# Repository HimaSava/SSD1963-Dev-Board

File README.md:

# SSD1963-Dev-Board

SSD1963 is a cheap LCD display chip. It is easy to use and it is preety cheap when compared to the others out there.
Unluckyly being cheap comes with it's flaws. The chip comes in a 128 pin QFP and is hard for beginners to solder without the right tools. But the biggest issue is PCB layout. Unless you are cutting corners on decaps the chip needs 40 seperate D-Caps.
And the worst part there is no guidelines of a dev board with any kind of layout out there to help the beginners.
Well through multiple revisions and sheer luck I designed the whole dev board and had it manufactured and tested.
To my surprise it works with out any hitchs. So I am sharing the files here. 

## Now some specs on the actual Dev Board:
It has the SSD1963 chip and also has the TSC2046 Touch Sensor chip.

The dev board was designed with a particular display(resistive touch) in mind and I have attached the datasheet for it. Based on your display you may need to change the LCD connector.

In interfacing the SSD1963 is used in 8080 mode(Check datasheet) and the touch sensor uses SPI protocol. For now I have added a FRC connector with all the pins that are needed to drive the board, if you want to change it be my guest.

Right now I am still making modifications to the board, so expect some changes in the future and also ping me if you have any suggestions.

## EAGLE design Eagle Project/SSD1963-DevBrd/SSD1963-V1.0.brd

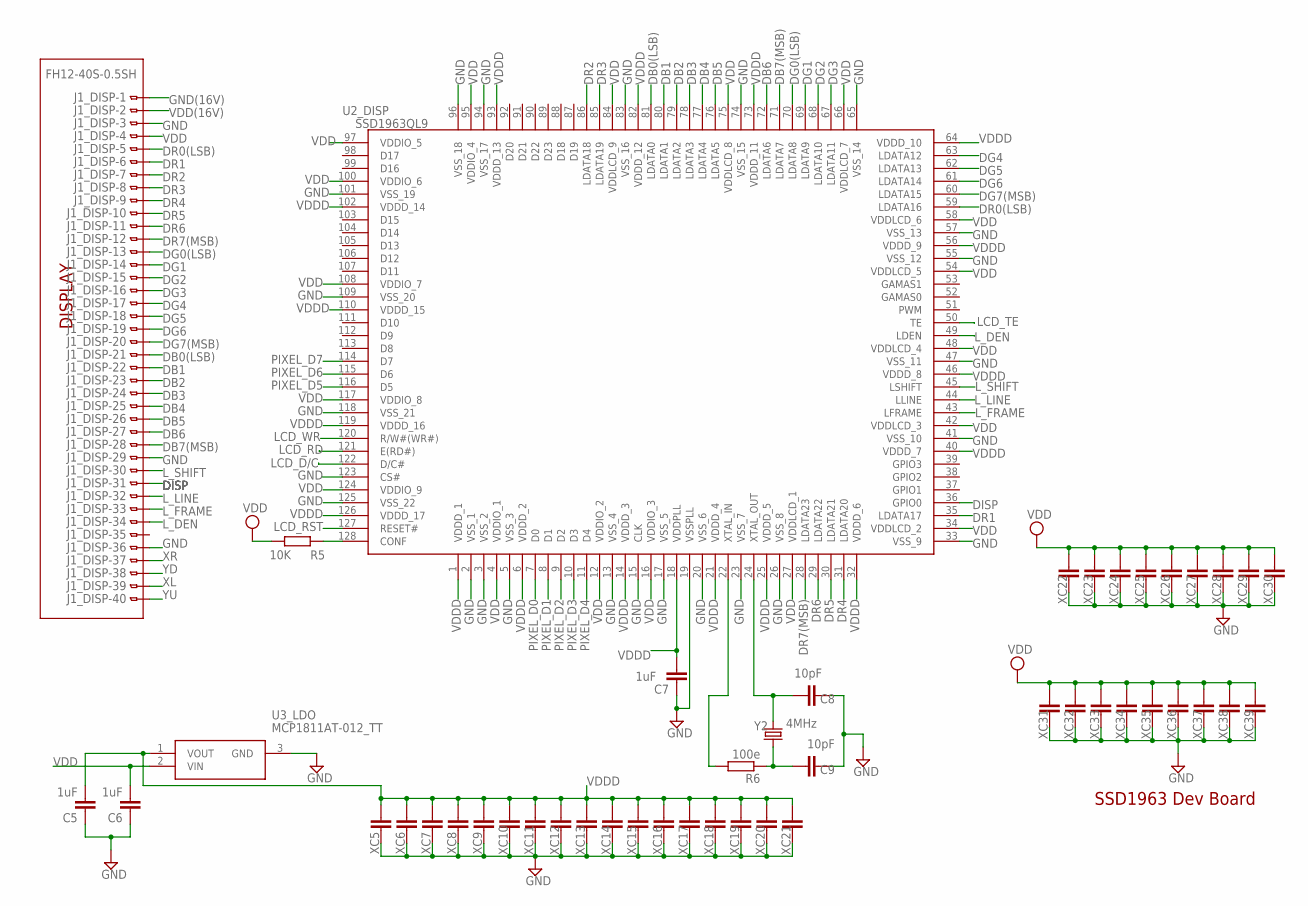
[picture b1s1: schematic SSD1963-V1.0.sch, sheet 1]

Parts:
C5, C6: 1uF; C1206
C7: 1uF; C0805
C8, C9: 10pF; C1206
J1_DISP: FH12-40S-0.5SH
R5: 10K; R1206
R6: 100e; R0805
U2_DISP: SSD1963QL9; QFP40P1600X1600X160-128N
U3_LDO: MCP1811AT-012_TT; SOT95P237X112-3N
XC5, XC6, XC7, XC8, XC9, XC10, XC11, XC12, XC13, XC14, XC15, XC16, XC17, XC18, XC19, XC20, XC21, XC22, XC23, XC24, XC25, XC26, XC27, XC28, XC29, XC30, XC31, XC32, XC33, XC34, XC35, XC36, XC37, XC38, XC39: 0.1uF; C0805
Y2: 4MHz; HC49UP

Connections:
DB0(LSB): J1_DISP.20, U2_DISP.81 (LDATA0)
DB1: J1_DISP.19, U2_DISP.80 (LDATA1)
DB2: J1_DISP.18, U2_DISP.79 (LDATA2)
DB3: J1_DISP.17, U2_DISP.78 (LDATA3)
DB4: J1_DISP.16, U2_DISP.77 (LDATA4)
DB5: J1_DISP.15, U2_DISP.76 (LDATA5)
DB6: J1_DISP.14, U2_DISP.72 (LDATA6)
DB7(MSB): J1_DISP.13, U2_DISP.71 (LDATA7)
DG0(LSB): J1_DISP.28, U2_DISP.70 (LDATA8)
DG1: J1_DISP.27, U2_DISP.69 (LDATA9)
DG2: J1_DISP.26, U2_DISP.68 (LDATA10)
DG3: J1_DISP.25, U2_DISP.67 (LDATA11)
DG4: J1_DISP.24, U2_DISP.63 (LDATA12)
DG5: J1_DISP.23, U2_DISP.62 (LDATA13)
DG6: J1_DISP.22, U2_DISP.61 (LDATA14)
DG7(MSB): J1_DISP.21, U2_DISP.60 (LDATA15)
DISP: J1_DISP.10, U2_DISP.36 (GPIO0)
DR0(LSB): J1_DISP.36, U2_DISP.59 (LDATA16)
DR1: J1_DISP.35, U2_DISP.35 (LDATA17)
DR2: J1_DISP.34, U2_DISP.86 (LDATA18)
DR3: J1_DISP.33, U2_DISP.85 (LDATA19)
DR4: J1_DISP.32, U2_DISP.31 (LDATA20)
DR5: J1_DISP.31, U2_DISP.30 (LDATA21)
DR6: J1_DISP.30, U2_DISP.29 (LDATA22)
DR7(MSB): J1_DISP.29, U2_DISP.28 (LDATA23)
GND: C5.1, C6.1, C7.1, C8.1, C9.1, J1_DISP.5, J1_DISP.12, J1_DISP.38, U2_DISP.2 (VSS_1), U2_DISP.3 (VSS_2), U2_DISP.5 (VSS_3), U2_DISP.13 (VSS_4), U2_DISP.15 (CLK), U2_DISP.17 (VSS_5), U2_DISP.19 (VSSPLL), U2_DISP.20 (VSS_6), U2_DISP.23 (VSS_7), U2_DISP.26 (VSS_8), U2_DISP.33 (VSS_9), U2_DISP.41 (VSS_10), U2_DISP.47 (VSS_11), U2_DISP.55 (VSS_12), U2_DISP.57 (VSS_13), U2_DISP.65 (VSS_14), U2_DISP.74 (VSS_15), U2_DISP.83 (VSS_16), U2_DISP.94 (VSS_17), U2_DISP.96 (VSS_18), U2_DISP.101 (VSS_19), U2_DISP.109 (VSS_20), U2_DISP.118 (VSS_21), U2_DISP.123 (CS#), U2_DISP.125 (VSS_22), U3_LDO.3 (GND), XC5.1, XC6.1, XC7.1, XC8.1, XC9.1, XC10.1, XC11.1, XC12.1, XC13.1, XC14.1, XC15.1, XC16.1, XC17.1, XC18.1, XC19.1, XC20.1, XC21.1, XC22.1, XC23.1, XC24.1, XC25.1, XC26.1, XC27.1, XC28.1, XC29.1, XC30.1, XC31.1, XC32.1, XC33.1, XC34.1, XC35.1, XC36.1, XC37.1, XC38.1, XC39.1; also elsewhere on the board
GND(16V): J1_DISP.40; also elsewhere on the board
LCD_D/C: U2_DISP.122 (D/C#); also elsewhere on the board
LCD_RD: U2_DISP.121 (E(RD#)); also elsewhere on the board
LCD_RST: U2_DISP.127 (RESET#); also elsewhere on the board
LCD_TE: U2_DISP.50 (TE); also elsewhere on the board
LCD_WR: U2_DISP.120 (R/W#(WR#)); also elsewhere on the board
L_DEN: J1_DISP.7, U2_DISP.49 (LDEN)
L_FRAME: J1_DISP.8, U2_DISP.43 (LFRAME)
L_LINE: J1_DISP.9, U2_DISP.44 (LLINE)
L_SHIFT: J1_DISP.11, U2_DISP.45 (LSHIFT)
unnamed: R5.1, U2_DISP.128 (CONF)
unnamed: C8.2, U2_DISP.24 (XTAL_OUT), Y2.2
unnamed: C9.2, R6.1, Y2.1
unnamed: R6.2, U2_DISP.22 (XTAL_IN)
PIXEL_D0: U2_DISP.7 (D0); also elsewhere on the board
PIXEL_D1: U2_DISP.8 (D1); also elsewhere on the board
PIXEL_D2: U2_DISP.9 (D2); also elsewhere on the board
PIXEL_D3: U2_DISP.10 (D3); also elsewhere on the board
PIXEL_D4: U2_DISP.11 (D4); also elsewhere on the board
PIXEL_D5: U2_DISP.116 (D5); also elsewhere on the board
PIXEL_D6: U2_DISP.115 (D6); also elsewhere on the board
PIXEL_D7: U2_DISP.114 (D7); also elsewhere on the board
VDD: C6.2, J1_DISP.37, R5.2, U2_DISP.4 (VDDIO_1), U2_DISP.12 (VDDIO_2), U2_DISP.16 (VDDIO_3), U2_DISP.27 (VDDLCD_1), U2_DISP.34 (VDDLCD_2), U2_DISP.42 (VDDLCD_3), U2_DISP.48 (VDDLCD_4), U2_DISP.54 (VDDLCD_5), U2_DISP.58 (VDDLCD_6), U2_DISP.66 (VDDLCD_7), U2_DISP.75 (VDDLCD_8), U2_DISP.84 (VDDLCD_9), U2_DISP.95 (VDDIO_4), U2_DISP.97 (VDDIO_5), U2_DISP.100 (VDDIO_6), U2_DISP.108 (VDDIO_7), U2_DISP.117 (VDDIO_8), U2_DISP.124 (VDDIO_9), U3_LDO.2 (VIN), XC22.2, XC23.2, XC24.2, XC25.2, XC26.2, XC27.2, XC28.2, XC29.2, XC30.2, XC31.2, XC32.2, XC33.2, XC34.2, XC35.2, XC36.2, XC37.2, XC38.2, XC39.2; also elsewhere on the board
VDD(16V): J1_DISP.39; also elsewhere on the board
VDDD: C5.2, C7.2, U2_DISP.1 (VDDD_1), U2_DISP.6 (VDDD_2), U2_DISP.14 (VDDD_3), U2_DISP.18 (VDDPLL), U2_DISP.21 (VDDD_4), U2_DISP.25 (VDDD_5), U2_DISP.32 (VDDD_6), U2_DISP.40 (VDDD_7), U2_DISP.46 (VDDD_8), U2_DISP.56 (VDDD_9), U2_DISP.64 (VDDD_10), U2_DISP.73 (VDDD_11), U2_DISP.82 (VDDD_12), U2_DISP.93 (VDDD_13), U2_DISP.102 (VDDD_14), U2_DISP.110 (VDDD_15), U2_DISP.119 (VDDD_16), U2_DISP.126 (VDDD_17), U3_LDO.1 (VOUT), XC5.2, XC6.2, XC7.2, XC8.2, XC9.2, XC10.2, XC11.2, XC12.2, XC13.2, XC14.2, XC15.2, XC16.2, XC17.2, XC18.2, XC19.2, XC20.2, XC21.2
XL: J1_DISP.2; also elsewhere on the board
XR: J1_DISP.4; also elsewhere on the board
YD: J1_DISP.3; also elsewhere on the board
YU: J1_DISP.1; also elsewhere on the board

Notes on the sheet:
DISPLAY
SSD1963 Dev Board

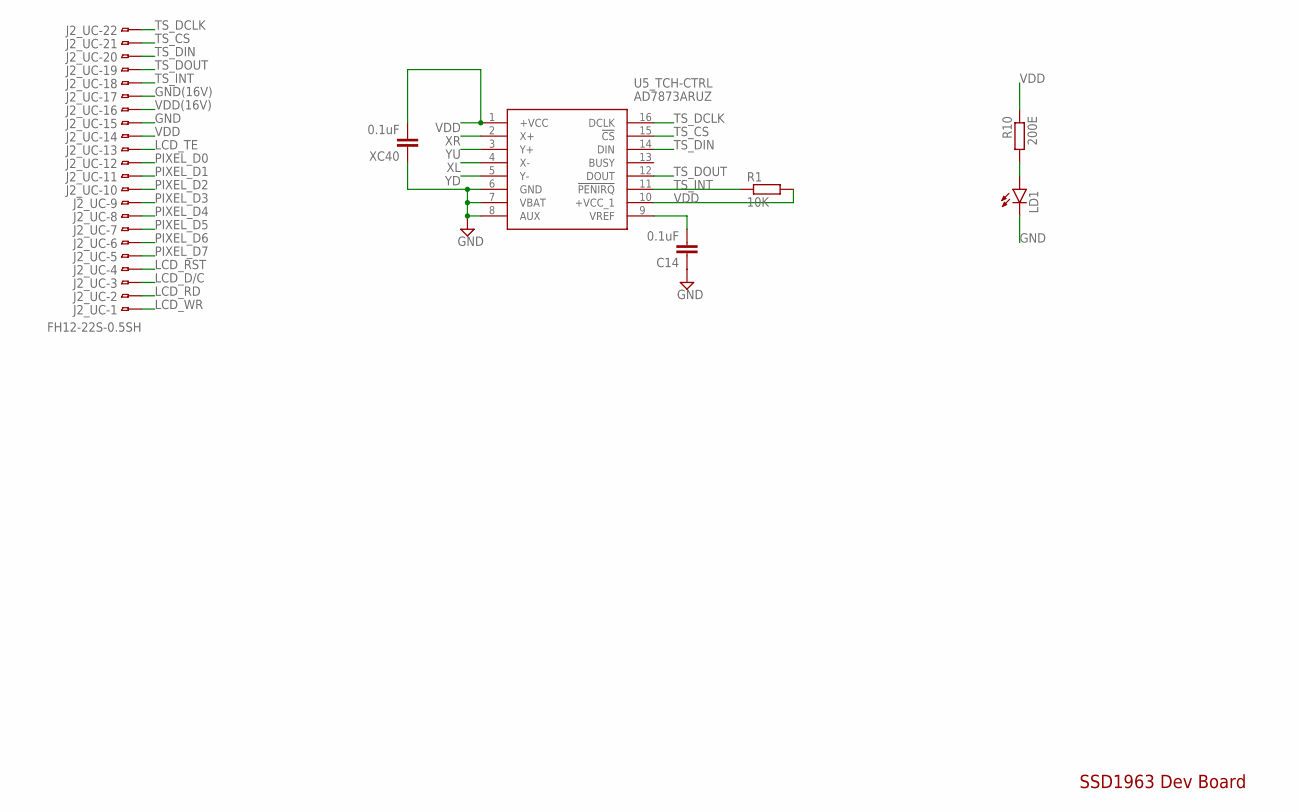
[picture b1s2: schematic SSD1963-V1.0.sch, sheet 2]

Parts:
C14: 0.1uF; C1206
J2_UC: FH12-22S-0.5SH
LD1: LEDCHIPLED_1206; CHIPLED_1206
R1: 10K; R1206
R10: 200E; R1206
U5_TCH-CTRL: AD7873ARUZ; SOP64P600X175-16N
XC40: 0.1uF; C0805

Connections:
GND: C14.1, J2_UC.15, LD1.C, U5_TCH-CTRL.6 (GND), U5_TCH-CTRL.7 (VBAT), U5_TCH-CTRL.8 (AUX), XC40.1; also elsewhere on the board
GND(16V): J2_UC.17; also elsewhere on the board
LCD_D/C: J2_UC.3; also elsewhere on the board
LCD_RD: J2_UC.2; also elsewhere on the board
LCD_RST: J2_UC.4; also elsewhere on the board
LCD_TE: J2_UC.13; also elsewhere on the board
LCD_WR: J2_UC.1; also elsewhere on the board
unnamed: C14.2, U5_TCH-CTRL.9 (VREF)
unnamed: LD1.A, R10.2
PIXEL_D0: J2_UC.12; also elsewhere on the board
PIXEL_D1: J2_UC.11; also elsewhere on the board
PIXEL_D2: J2_UC.10; also elsewhere on the board
PIXEL_D3: J2_UC.9; also elsewhere on the board
PIXEL_D4: J2_UC.8; also elsewhere on the board
PIXEL_D5: J2_UC.7; also elsewhere on the board
PIXEL_D6: J2_UC.6; also elsewhere on the board
PIXEL_D7: J2_UC.5; also elsewhere on the board
TS_CS: J2_UC.21, U5_TCH-CTRL.15 (!CS)
TS_DCLK: J2_UC.22, U5_TCH-CTRL.16 (DCLK)
TS_DIN: J2_UC.20, U5_TCH-CTRL.14 (DIN)
TS_DOUT: J2_UC.19, U5_TCH-CTRL.12 (DOUT)
TS_INT: J2_UC.18, R1.1, U5_TCH-CTRL.11 (!PENIRQ)
VDD: J2_UC.14, R1.2, R10.1, U5_TCH-CTRL.1 (+VCC), U5_TCH-CTRL.10 (+VCC_1), XC40.2; also elsewhere on the board
VDD(16V): J2_UC.16; also elsewhere on the board
XL: U5_TCH-CTRL.4 (X-); also elsewhere on the board
XR: U5_TCH-CTRL.2 (X+); also elsewhere on the board
YD: U5_TCH-CTRL.5 (Y-); also elsewhere on the board
YU: U5_TCH-CTRL.3 (Y+); also elsewhere on the board

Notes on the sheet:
SSD1963 Dev Board

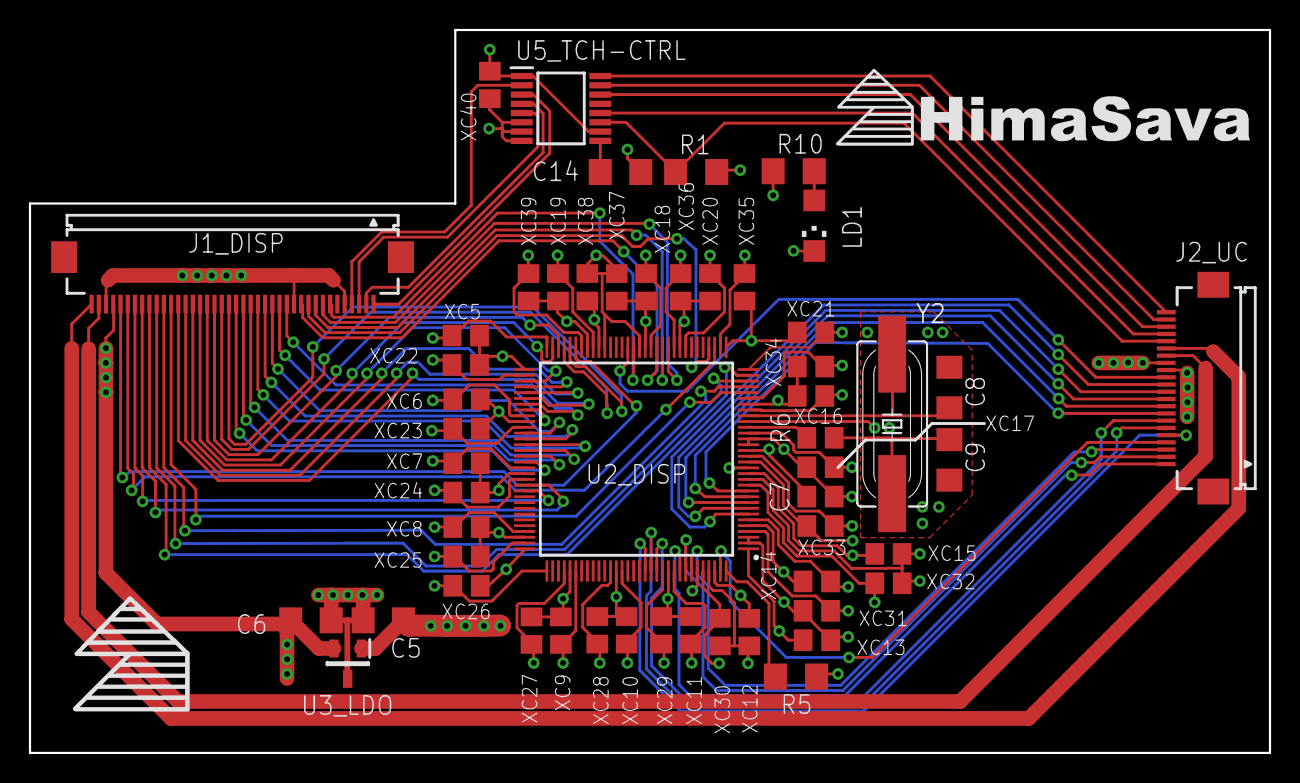
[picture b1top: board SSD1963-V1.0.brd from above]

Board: 4 copper layers, 85.8 x 50.0 mm, 53 parts (0 on the bottom side), 62 nets.

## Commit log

2020-12-09 Adding basic files
2020-12-09 Removing eagle backup files
